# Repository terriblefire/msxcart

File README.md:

# MSX Cartridge - Simple CPLD-Based MegaROM Mapper

A minimalist MSX cartridge design based on the Xilinx XC9536XL CPLD, implementing a standard MegaROM mapper for bank-switched ROM cartridges.

---

## Discord

https://discord.gg/aXGkKWJQ

## ⚠️ Project Status - SUPERSEDED

**This project has been superseded by the RISKYMSX project** ([arkadiuszmakarenko/RISKYMSX](https://github.com/arkadiuszmakarenko/RISKYMSX)).

### 🎯 **We recommend building RISKYMSX instead**

RISKYMSX is a modern, feature-rich MSX cartridge solution that offers significant advantages over this simple CPLD design:

### Why Choose RISKYMSX

| Feature | RISKYMSX (Recommended) | MSX Cartridge (This Project) |
|---------|------------------------|------------------------------|
| **ROM Loading** | USB pen drive, hot-swappable | Requires ROM programmer |
| **ROM Capacity** | Up to 256KB | Up to 256KB |
| **SCC Support** | Software SCC emulation | None |
| **Convenience** | Change ROMs instantly via USB | Must reprogram ROM chip |
| **Modern MCU** | RISC-V CH32V303 | Legacy CPLD |
| **Firmware Updates** | USB or WCH-LinkE | JTAG programmer |
| **Mapper Support** | Konami, ASCII 8K/16K, Neo, SCC | Konami, ASCII 8K/16K |
| **User Experience** | Plug and play with USB drive | Requires hardware tools |

**👉 For new builds, please use [RISKYMSX](https://github.com/arkadiuszmakarenko/RISKYMSX)** - it provides better functionality, easier ROM management, and a superior user experience.

### About This Archive

This repository remains available for:
- Historical reference
- Educational purposes (learning CPLD design)
- Users who already built this hardware
- Those who need the absolute simplest possible design

However, for any new MSX cartridge project, RISKYMSX is the superior choice.

---

## Features

- **Xilinx XC9536XL CPLD** - Small, reliable, low-cost programmable logic
- **Standard MegaROM Mapper** - 4 switchable ROM pages (8KB each)
- **MSX Compatible** - Works with all MSX computers
- **Simple Design** - Minimal component count, easy to build
- **Open Source** - GPL v3 licensed hardware and HDL
- **Automated Build System** - Docker-based builds for firmware and PCB manufacturing files

## Hardware Specifications

- **Target Device**: Xilinx XC9536XL-10-VQ44 CPLD
- **Interface**: MSX cartridge slot (Z80 bus compatible)
- **Memory Mapping**: 4 page registers for bank switching
- **ROM Size**: Supports up to 512KB (limited by CPLD I/O)
- **Power**: 5V from MSX cartridge slot

## Memory Map

The mapper implements standard MSX MegaROM banking:

| Address Range | Page | Function |
|---------------|------|----------|
| `0x4000-0x5FFF` | 0 | Fixed to bank 0 |
| `0x6000-0x7FFF` | 1 | Switchable (register 1) |
| `0x8000-0x9FFF` | 2 | Switchable (register 2) |
| `0xA000-0xBFFF` | 3 | Switchable (register 3) |

Bank switching is performed by writing to specific memory addresses during M1 cycle.

## Building

### Prerequisites

- Docker (for building firmware and PCB files)
- Git (for version control)
- Make (for build automation)

### Build Firmware

```bash
# Build CPLD firmware
make -C boards

# Output: boards/msxcart_YYYY_MM_DD_GITHASH.zip
```

### Generate PCB Manufacturing Files

```bash
# Generate Gerber files
make -C eagle gerbers

# Generate BOM and CPL for assembly
make -C eagle assembly

# Generate PDF schematic
make -C eagle pdf
```

## Manufacturing

### PCB Fabrication

1. Use the Gerber ZIP from `eagle/tfcart_*.zip` to order PCBs from your preferred manufacturer (JLCPCB, PCBWay, etc.)
2. The design is a 4-layer board optimized for standard PCB processes

### PCB Assembly

1. Use `eagle/tfcart_bom.csv` (Bill of Materials) for component ordering
2. Use `eagle/tfcart_cpl.csv` (Component Placement List) if using assembly services
3. Alternatively, hand-solder components - the board is designed for easy assembly

### Programming the CPLD

1. Connect a JTAG programmer to the CPLD
2. Flash the `.jed` file from `boards/msxcartr1/msxcartr1_top.jed`
3. Use Xilinx iMPACT or xc3sprog for programming

### Programming the ROM

1. Program your ROM chip with the desired MSX ROM image
2. Install the ROM chip in the socket
3. Insert into MSX cartridge slot

## Project Structure

```
msxcart/
├── rtl/                    # Verilog HDL source files
│   ├── msxcart_top.v      # Top-level module
│   └── mapper.v           # Memory mapper logic
├── boards/                 # CPLD build configuration
│   ├── msxcartr1/         # Revision 1 board files
│   │   ├── Makefile       # Board-specific build
│   │   └── msxcartr1.ucf  # Pin constraints
│   ├── Makefile           # Top-level build
│   ├── Makefile.inc       # Docker environment
│   └── Makefile.cpld      # Xilinx ISE flow
├── eagle/                  # PCB design files
│   ├── tfcart.brd         # Eagle board file
│   ├── tfcart.sch         # Eagle schematic
│   ├── Makefile           # PCB build automation
│   ├── extract_bom.py     # BOM extraction script
│   └── extract_cpl.py     # CPL extraction script
└── .github/workflows/      # CI/CD automation
    ├── actions.yml         # Firmware build
    ├── gerbers.yml         # Gerber generation
    ├── generate_assembly.yml # BOM/CPL generation
    ├── schematic-pdf.yml   # PDF schematic
    └── release.yml         # Release packaging
```

## Development

### Build System

The project uses Docker containers for reproducible builds:

- `terriblefire78/xilinx:v1` - Xilinx ISE 10.1 for CPLD synthesis
- `terriblefire78/eagle:v1` - Eagle CAM for Gerber generation
- `terriblefire78/eagle-pdf` - PDF schematic generation

### Modifying the Design

1. Edit Verilog files in `rtl/`
2. Adjust pin assignments in `boards/msxcartr1/msxcartr1.ucf`
3. Build and test: `make -C boards`
4. The build system automatically handles Docker environment

### Testing

Flash the generated `.jed` file to your CPLD and test with an MSX computer. The mapper should properly switch ROM banks when games access the appropriate memory addresses.

## GitHub Actions

The repository includes automated workflows:

- **Firmware Build** - Builds CPLD firmware on code changes
- **Gerber Generation** - Creates PCB manufacturing files
- **Assembly Files** - Generates BOM and CPL
- **Schematic PDF** - Produces documentation
- **Release Packaging** - Creates complete release bundles

Releases are automatically created when you push a git tag:

```bash
git tag -a v1.0 -m "Release version 1.0"
git push origin v1.0
```

## License

This project is licensed under the GNU General Public License v3.0 - see the [LICENSE](LICENSE) file for details.

Copyright (C) 2021-2025 Stephen J. Leary

## Acknowledgments

- Original design concept by Stephen J. Leary
- Inspired by the MSX community's dedication to preserving retro computing

## Related Projects

- **[RISKYMSX](https://github.com/arkadiuszmakarenko/RISKYMSX)** - Feature-rich USB-programmable MSX cartridge with SCC emulation

## Contributing

Contributions are welcome! Please feel free to submit pull requests or open issues for bugs and feature requests.

## Support

For questions, issues, or discussions:

1. Open an issue on GitHub
2. Check existing issues for solutions
3. Review the MSX community forums for related discussions

---

**Note**: This is a hardware project. Users must have appropriate skills for PCB assembly and CPLD programming. This design is provided as-is for educational and hobbyist purposes.

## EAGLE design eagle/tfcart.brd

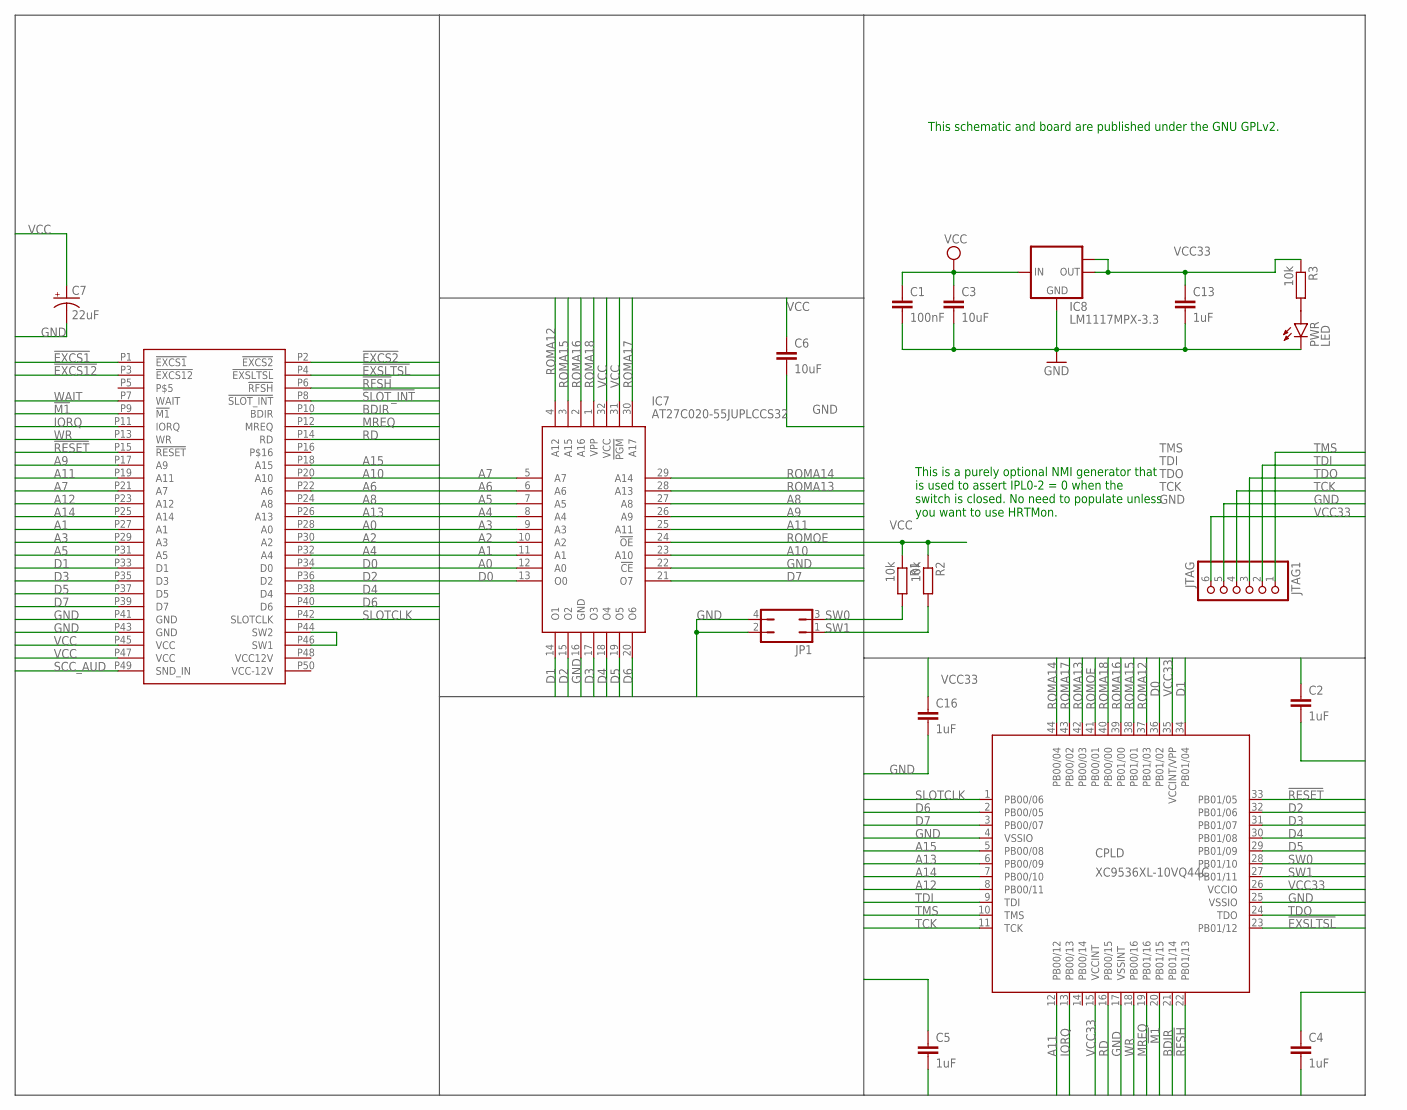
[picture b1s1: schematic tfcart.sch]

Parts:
C1: 100nF; C1206
C2, C4, C5, C16: 1uF; C0603
C3, C6: 10uF; C0603
C7: 22uF; PANASONIC_B
C13: 1uF; C1206
CN1: MSX_CART
CPLD: XC9536XL-10VQ44C; SQFP-S-10X10-44
IC7: AT27C020-55JUPLCCS32; PLCC-S32
IC8: LM1117MPX-3.3; SOT223
JP1: JP2Q
JTAG1: JTAG; 1X06_ROUND
PWR: LED; SML0805
R1, R2, R3: 10k; R0603

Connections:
!EXCS1: CN1.P1 (!EXCS1)
!EXCS2: CN1.P2 (!EXCS2)
!EXCS12: CN1.P3 (!EXCS12)
!EXSLTSL: CN1.P4 (!EXSLTSL), CPLD.23 (PB01/12)
!M1: CN1.P9 (!M1), CPLD.20 (PB01/15)
!RESET: CN1.P15 (!RESET), CPLD.33 (PB01/05)
!RFSH: CN1.P6 (!RFSH), CPLD.22 (PB01/13)
!SLOT_INT: CN1.P8 (!SLOT_INT)
A0: CN1.P28 (A0), IC7.12 (A0)
A1: CN1.P27 (A1), IC7.11 (A1)
A2: CN1.P30 (A2), IC7.10 (A2)
A3: CN1.P29 (A3), IC7.9 (A3)
A4: CN1.P32 (A4), IC7.8 (A4)
A5: CN1.P31 (A5), IC7.7 (A5)
A6: CN1.P22 (A6), IC7.6 (A6)
A7: CN1.P21 (A7), IC7.5 (A7)
A8: CN1.P24 (A8), IC7.27 (A8)
A9: CN1.P17 (A9), IC7.26 (A9)
A10: CN1.P20 (A10), IC7.23 (A10)
A11: CN1.P19 (A11), CPLD.12 (PB00/12), IC7.25 (A11)
A12: CN1.P23 (A12), CPLD.8 (PB00/11)
A13: CN1.P26 (A13), CPLD.6 (PB00/09)
A14: CN1.P25 (A14), CPLD.7 (PB00/10)
A15: CN1.P18 (A15), CPLD.5 (PB00/08)
BDIR: CN1.P10 (BDIR), CPLD.21 (PB01/14)
D0: CN1.P34 (D0), CPLD.36 (PB01/02), IC7.13 (O0)
D1: CN1.P33 (D1), CPLD.34 (PB01/04), IC7.14 (O1)
D2: CN1.P36 (D2), CPLD.32 (PB01/06), IC7.15 (O2)
D3: CN1.P35 (D3), CPLD.31 (PB01/07), IC7.17 (O3)
D4: CN1.P38 (D4), CPLD.30 (PB01/08), IC7.18 (O4)
D5: CN1.P37 (D5), CPLD.29 (PB01/09), IC7.19 (O5)
D6: CN1.P40 (D6), CPLD.2 (PB00/05), IC7.20 (O6)
D7: CN1.P39 (D7), CPLD.3 (PB00/07), IC7.21 (O7)
GND: C1.2, C2.2, C3.2, C4.2, C5.2, C6.2, C7.-, C13.2, C16.2, CN1.P41 (GND), CN1.P43 (GND), CPLD.4 (VSSIO), CPLD.17 (VSSINT), CPLD.25 (VSSIO), IC7.16 (GND), IC7.22 (!CE), IC8.1 (GND), JP1.2, JP1.4, JTAG1.5, PWR.C
IORQ: CN1.P11 (IORQ), CPLD.13 (PB00/13)
MREQ: CN1.P12 (MREQ), CPLD.19 (PB01/16)
unnamed: CN1.P44 (SW2), CN1.P46 (SW1)
unnamed: PWR.A, R3.2
RD: CN1.P14 (RD), CPLD.16 (PB00/15)
ROMA12: CPLD.37 (PB01/03), IC7.4 (A12)
ROMA13: CPLD.42 (PB00/03), IC7.28 (A13)
ROMA14: CPLD.44 (PB00/04), IC7.29 (A14)
ROMA15: CPLD.38 (PB01/01), IC7.3 (A15)
ROMA16: CPLD.39 (PB01/00), IC7.2 (A16)
ROMA17: CPLD.43 (PB00/02), IC7.30 (A17)
ROMA18: CPLD.40 (PB00/00), IC7.1 (VPP)
ROMOE: CPLD.41 (PB00/01), IC7.24 (!OE)
SCC_AUD: CN1.P49 (SND_IN)
SLOTCLK: CN1.P42 (SLOTCLK), CPLD.1 (PB00/06)
SW0: CPLD.28 (PB01/10), JP1.3, R1.2
SW1: CPLD.27 (PB01/11), JP1.1, R2.2
TCK: CPLD.11 (TCK), JTAG1.4
TDI: CPLD.9 (TDI), JTAG1.2
TDO: CPLD.24 (TDO), JTAG1.3
TMS: CPLD.10 (TMS), JTAG1.1
VCC: C1.1, C3.1, C6.1, C7.+, CN1.P45 (VCC), CN1.P47 (VCC), IC7.31 (!PGM), IC7.32 (VCC), IC8.3 (IN), R1.1, R2.1
VCC33: C2.1, C4.1, C5.1, C13.1, C16.1, CPLD.15 (VCCINT), CPLD.26 (VCCIO), CPLD.35 (VCCINT/VPP), IC8.2 (OUT), IC8.TAB (OUT1), JTAG1.6, R3.1
WAIT: CN1.P7 (WAIT)
WR: CN1.P13 (WR), CPLD.18 (PB00/16)

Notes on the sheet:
This is a purely optional NMI generator that is used to assert IPL0-2 = 0 when the switch is closed. No need to populate unless you want to use HRTMon.
This schematic and board are published under the GNU GPLv2.

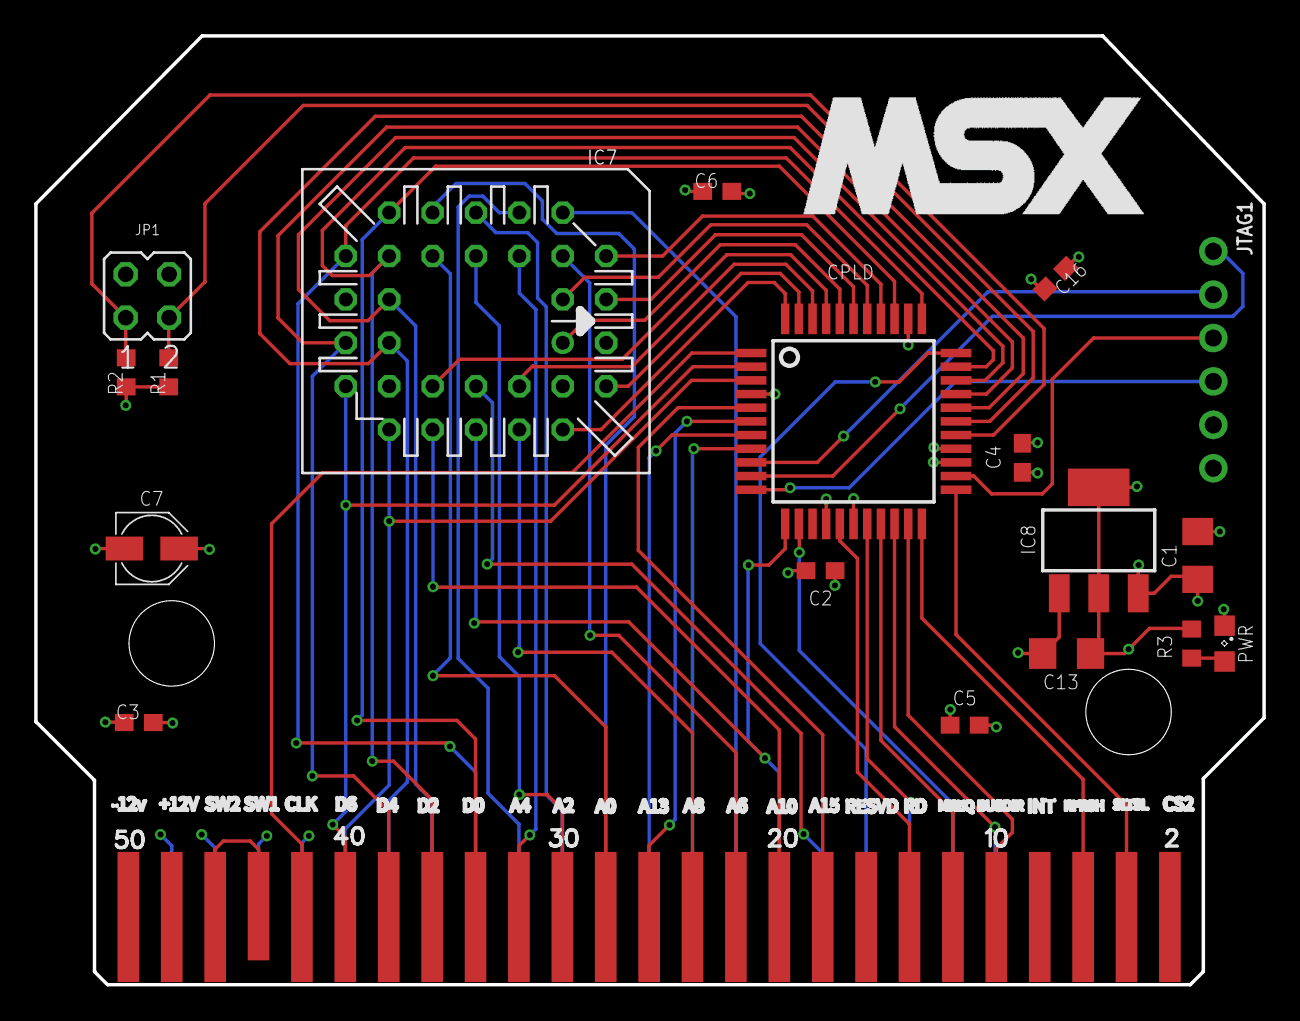
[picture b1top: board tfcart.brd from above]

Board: 4 copper layers, 71.9 x 55.5 mm, 19 parts (0 on the bottom side), 53 nets.

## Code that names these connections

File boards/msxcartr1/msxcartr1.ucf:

# Copyright (C) 2016-2025 Stephen J. Leary
# All rights reserved.
#
# This file is part of MSX Cartridge (msxcart)
#
# MSX Cartridge is free software: you can redistribute it and/or modify
# it under the terms of the GNU General Public License as published by
# the Free Software Foundation, either version 3 of the License, or
# (at your option) any later version.
#
# MSX Cartridge is distributed in the hope that it will be useful,
# but WITHOUT ANY WARRANTY; without even the implied warranty of
# MERCHANTABILITY or FITNESS FOR A PARTICULAR PURPOSE.  See the
# GNU General Public License for more details.
#
# You should have received a copy of the GNU General Public License
# along with MSX Cartridge. If not, see <http://www.gnu.org/licenses/>.

NET "EXSLTSL"      LOC="23";
NET "M1"       LOC="20";
NET "RESET"      LOC="33";
NET "RFSH"      LOC="22";
NET "A<12>"      LOC="8";
NET "A<13>"      LOC="6";
NET "A<14>"      LOC="7";
NET "A<15>"      LOC="5";
NET "BDIR"      LOC="21";
NET "D<0>"      LOC="36";
NET "D<1>"      LOC="34";
NET "D<2>"      LOC="32";
NET "D<3>"      LOC="31";
NET "D<4>"      LOC="30";
NET "D<5>"      LOC="29";
NET "D<6>"      LOC="2";
NET "D<7>"      LOC="3";
NET "IORQ"      LOC="13";
NET "MREQ"      LOC="19";
NET "RD"      LOC="16";
NET "ROMA<12>"      LOC="37";
NET "ROMA<13>"      LOC="42";
NET "ROMA<14>"      LOC="44";
NET "ROMA<15>"      LOC="38";
NET "ROMA<16>"      LOC="39";
NET "ROMA<17>"      LOC="43";
NET "ROMA<18>"      LOC="40";
NET "ROMOE"      LOC="41";
NET "SLOTCLK"      LOC="1";
NET "SW<0>"      LOC="28";
NET "SW<1>"      LOC="27";
NET "WR"      LOC="18";

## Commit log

2023-06-24 initial commit. missing drills
2023-07-12 First working version
2023-07-13 fixed the drills fixed the corners changed the dip switches for jumpers.
2025-02-23 fixing the docker build and commiting everyting
2025-02-23 update workflow
2025-11-19 MSX Cartridge v1.0 - Complete CPLD-based MegaROM implementation
    A minimalist MSX cartridge design based on Xilinx XC9536XL CPLD with
    complete build automation and manufacturing outputs.
    NOTE: This project has been superseded by RISKYMSX. For new builds,
    please use https://github.com/arkadiuszmakarenko/RISKYMSX which offers
    superior features including USB ROM loading, SCC emulation, and better
    user experience.
2025-11-19 Update README with Discord link and project status
    Added Discord link and updated project status to superseded.
2025-11-19 removed redundant text from schematic
2025-11-19 fixing minor details
2025-11-19 Revise README for project supersession and recommendations
    Updated README to reflect project status as superseded by RISKYMSX, including feature comparisons and recommendations.

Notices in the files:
README.md:
License: GPL v3
parts and their libraries:
microbuilder: This work is placed in the public domain, and may be freely used for commercial and non-commercial work with the following conditions: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
